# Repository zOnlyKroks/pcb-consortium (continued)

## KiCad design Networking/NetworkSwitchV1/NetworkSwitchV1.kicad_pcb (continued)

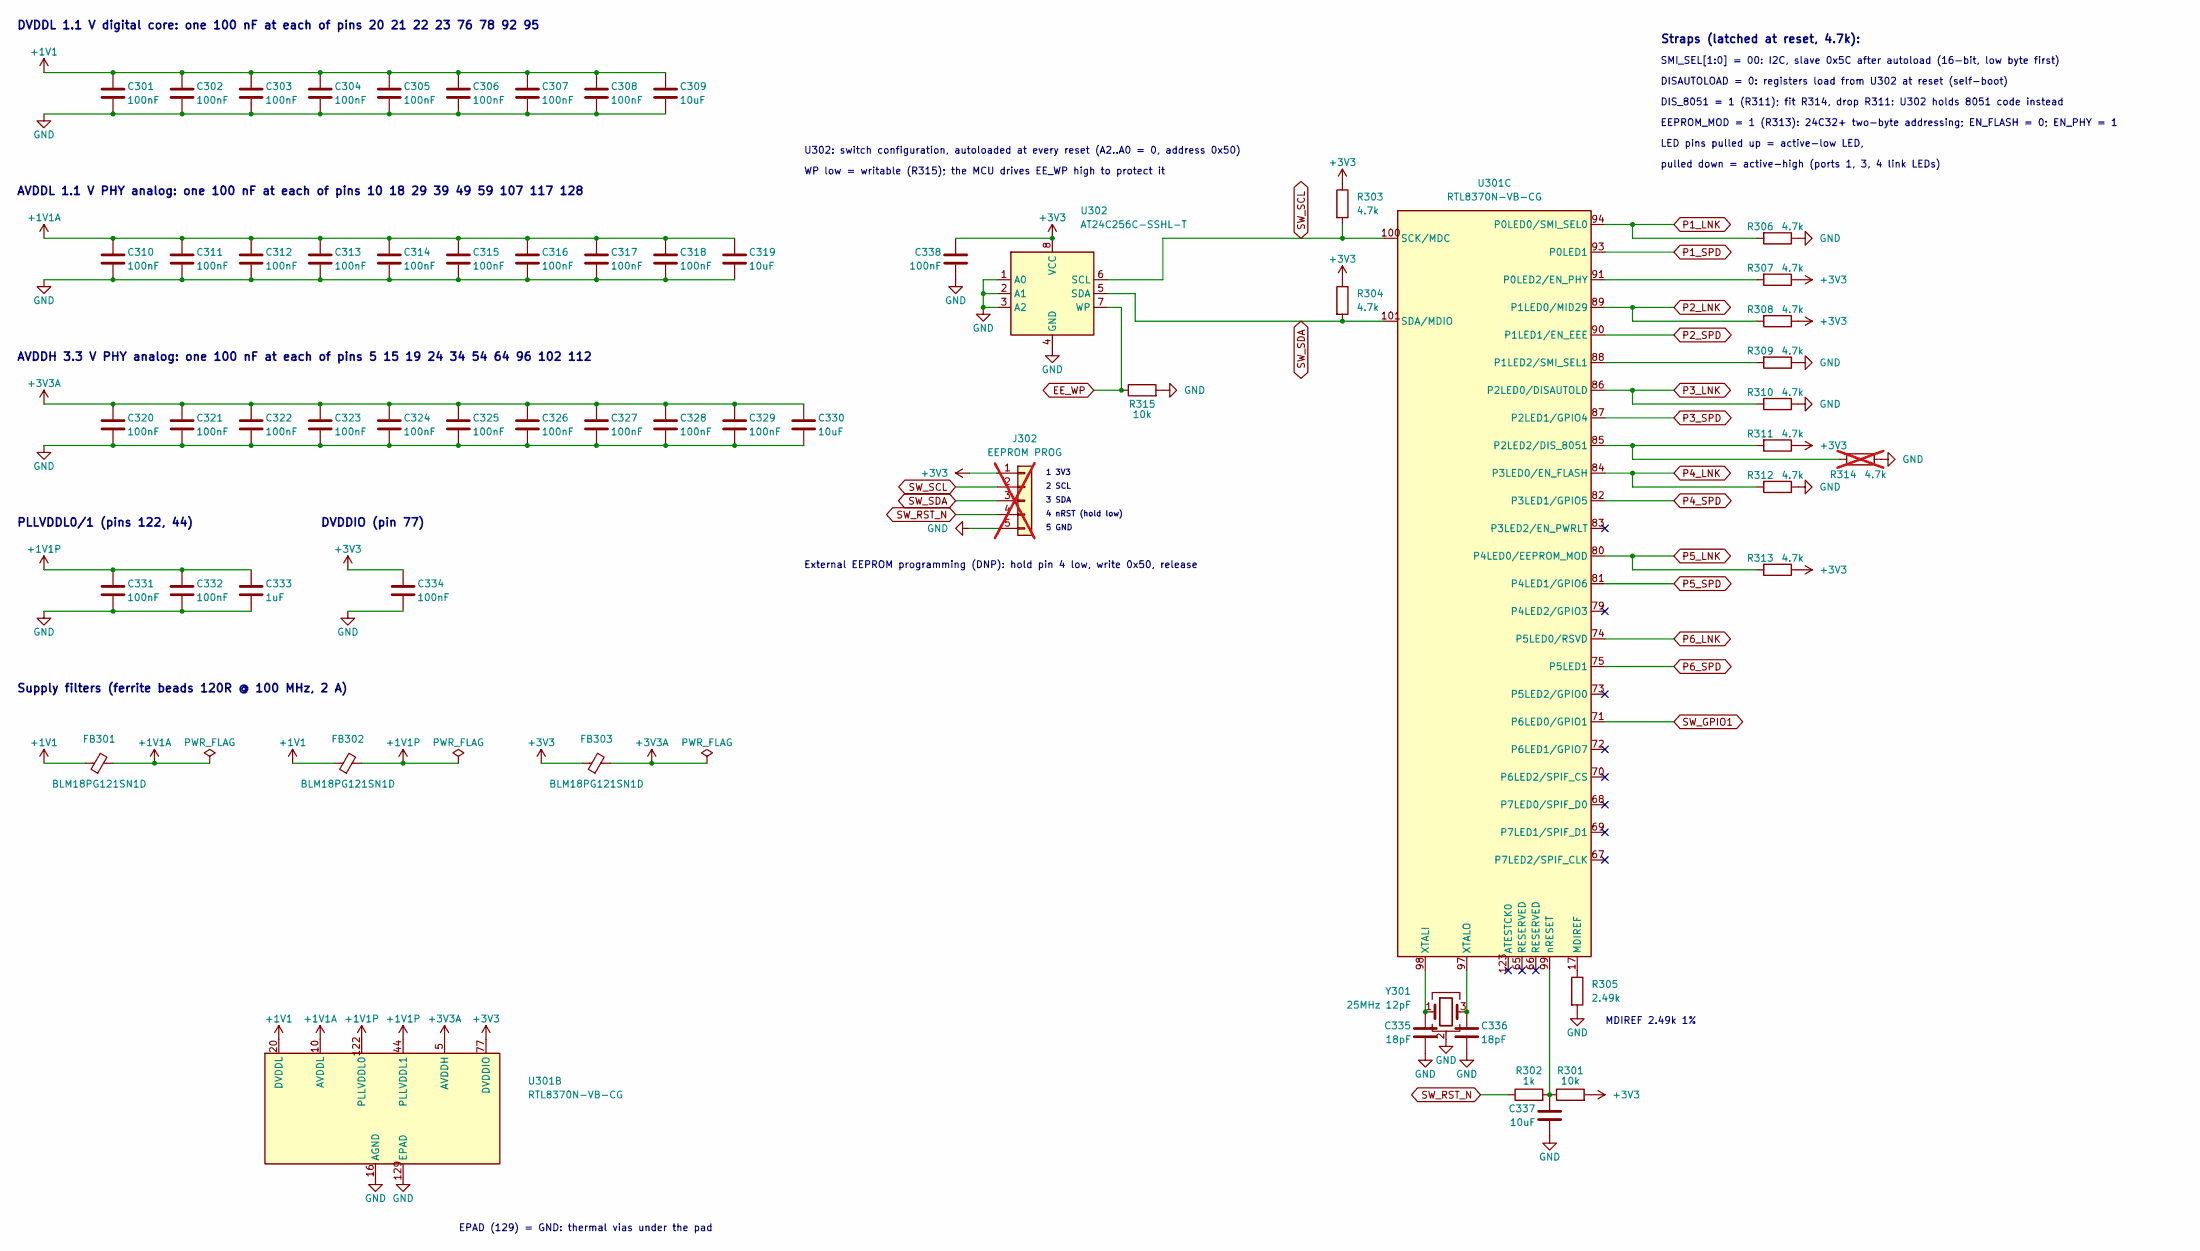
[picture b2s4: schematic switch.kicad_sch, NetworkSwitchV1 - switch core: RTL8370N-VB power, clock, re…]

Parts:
C301, C302, C303, C304, C305, C306, C307, C308, C310, C311, C312, C313, C314, C315, C316, C317, C318, C320, C321, C322, C323, C324, C325, C326, C327, C328, C329, C331, C332, C334, C338: 100nF; C_0603_1608Metric; LCSC Part # C14663
C309, C319, C330, C337: 10uF; C_0603_1608Metric; LCSC Part # C19702
C333: 1uF; C_0603_1608Metric; LCSC Part # C15849
C335, C336: 18pF; C_0603_1608Metric; LCSC Part # C1647
FB301, FB302, FB303: BLM18PG121SN1D; L_0603_1608Metric; LCSC Part # C14709
J302: EEPROM PROG; PinHeader_1x05_P2.54mm_Vertical; LCSC Part # C492404; not fitted
R301, R315: 10k; R_0603_1608Metric; LCSC Part # C25804
R302: 1k; R_0603_1608Metric; LCSC Part # C21190
R303, R304, R306, R307, R308, R309, R310, R311, R312, R313: 4.7k; R_0603_1608Metric; LCSC Part # C23162
R305: 2.49k; R_0603_1608Metric; LCSC Part # C22908
R314: 4.7k; R_0603_1608Metric; LCSC Part # C23162; not fitted
U301: RTL8370N-VB-CG; LQFP-128_L20.0-W14.0-P0.50-BL-EP7.0; LCSC Part # C2803243
U302: AT24C256C-SSHL-T; SOIC-8_3.9x4.9mm_P1.27mm; LCSC Part # C6482
Y301: 25MHz 12pF; Crystal_SMD_3225-4Pin_3.2x2.5mm; MPN X322525MOB4SI; LCSC Part # C9006

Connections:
+1V1: C301.1, C302.1, C303.1, C304.1, C305.1, C306.1, C307.1, C308.1, C309.1, FB301.1, FB302.1, U301.20 (DVDDL), U301.21 (DVDDL), U301.22 (DVDDL), U301.23 (DVDDL), U301.76 (DVDDL), U301.78 (DVDDL), U301.92 (DVDDL), U301.95 (DVDDL); also elsewhere on the board
+1V1A: C310.1, C311.1, C312.1, C313.1, C314.1, C315.1, C316.1, C317.1, C318.1, C319.1, FB301.2, U301.10 (AVDDL), U301.18 (AVDDL), U301.29 (AVDDL), U301.39 (AVDDL), U301.49 (AVDDL), U301.59 (AVDDL), U301.107 (AVDDL), U301.117 (AVDDL), U301.128 (AVDDL)
+1V1P: C331.1, C332.1, C333.1, FB302.2, U301.44 (PLLVDDL1), U301.122 (PLLVDDL0)
+3V3: C334.1, C338.1, FB303.1, J302.1, R301.2, R303.1, R304.1, R307.1, R308.1, R311.1, R313.1, U301.77 (DVDDIO), U302.8 (VCC); also elsewhere on the board
+3V3A: C320.1, C321.1, C322.1, C323.1, C324.1, C325.1, C326.1, C327.1, C328.1, C329.1, C330.1, FB303.2, U301.5 (AVDDH), U301.15 (AVDDH), U301.19 (AVDDH), U301.24 (AVDDH), U301.34 (AVDDH), U301.54 (AVDDH), U301.64 (AVDDH), U301.96 (AVDDH), U301.102 (AVDDH), U301.112 (AVDDH)
EE_WP: R315.1, U302.7 (WP); also elsewhere on the board
GND: C301.2, C302.2, C303.2, C304.2, C305.2, C306.2, C307.2, C308.2, C309.2, C310.2, C311.2, C312.2, C313.2, C314.2, C315.2, C316.2, C317.2, C318.2, C319.2, C320.2, C321.2, C322.2, C323.2, C324.2, C325.2, C326.2, C327.2, C328.2, C329.2, C330.2, C331.2, C332.2, C333.2, C334.2, C335.2, C336.2, C337.2, C338.2, J302.5, R305.2, R306.1, R309.1, R310.1, R312.1, R314.1, R315.2, U301.16 (AGND), U301.129 (EPAD), U302.1 (A0), U302.2 (A1), U302.3 (A2), U302.4 (GND), Y301.2 (G), Y301.4 (G); also elsewhere on the board
unnamed: R305.1, U301.17 (MDIREF)
unnamed: R307.2, U301.91 (P0LED2/EN_PHY)
unnamed: R309.2, U301.88 (P1LED2/SMI_SEL1)
unnamed: R311.2, R314.2, U301.85 (P2LED2/DIS_8051)
unnamed: C335.1, U301.98 (XTALI), Y301.1
unnamed: C336.1, U301.97 (XTALO), Y301.3
unnamed: C337.1, R301.1, R302.2, U301.99 (nRESET)
P1_LNK: R306.2, U301.94 (P0LED0/SMI_SEL0); also elsewhere on the board
P1_SPD: U301.93 (P0LED1); also elsewhere on the board
P2_LNK: R308.2, U301.89 (P1LED0/MID29); also elsewhere on the board
P2_SPD: U301.90 (P1LED1/EN_EEE); also elsewhere on the board
P3_LNK: R310.2, U301.86 (P2LED0/DISAUTOLD); also elsewhere on the board
P3_SPD: U301.87 (P2LED1/GPIO4); also elsewhere on the board
P4_LNK: R312.2, U301.84 (P3LED0/EN_FLASH); also elsewhere on the board
P4_SPD: U301.82 (P3LED1/GPIO5); also elsewhere on the board
P5_LNK: R313.2, U301.80 (P4LED0/EEPROM_MOD); also elsewhere on the board
P5_SPD: U301.81 (P4LED1/GPIO6); also elsewhere on the board
P6_LNK: U301.74 (P5LED0/RSVD); also elsewhere on the board
P6_SPD: U301.75 (P5LED1); also elsewhere on the board
SW_GPIO1: U301.71 (P6LED0/GPIO1); also elsewhere on the board
SW_RST_N: J302.4, R302.1; also elsewhere on the board
SW_SCL: J302.2, R303.2, U301.100 (SCK/MDC), U302.6 (SCL); also elsewhere on the board
SW_SDA: J302.3, R304.2, U301.101 (SDA/MDIO), U302.5 (SDA); also elsewhere on the board

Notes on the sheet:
DVDDIO (pin 77)
DVDDL 1.1 V digital core: one 100 nF at each of pins 20 21 22 23 76 78 92 95
1 3V3
Supply filters (ferrite beads 120R @ 100 MHz, 2 A)
DIS_8051 = 1 (R311); fit R314, drop R311: U302 holds 8051 code instead
LED pins pulled up = active-low LED,
AVDDL 1.1 V PHY analog: one 100 nF at each of pins 10 18 29 39 49 59 107 117 128
EPAD (129) = GND: thermal vias under the pad
Straps (latched at reset, 4.7k):
5 GND
PLLVDDL0/1 (pins 122, 44)
U302: switch configuration, autoloaded at every reset (A2..A0 = 0, address 0x50)
SMI_SEL[1:0] = 00: I2C, slave 0x5C after autoload (16-bit, low byte first)
MDIREF 2.49k 1%
pulled down = active-high (ports 1, 3, 4 link LEDs)
AVDDH 3.3 V PHY analog: one 100 nF at each of pins 5 15 19 24 34 54 64 96 102 112
External EEPROM programming (DNP): hold pin 4 low, write 0x50, release
WP low = writable (R315); the MCU drives EE_WP high to protect it
DISAUTOLOAD = 0: registers load from U302 at reset (self-boot)
3 SDA
EEPROM_MOD = 1 (R313): 24C32+ two-byte addressing; EN_FLASH = 0; EN_PHY = 1
4 nRST (hold low)
2 SCL

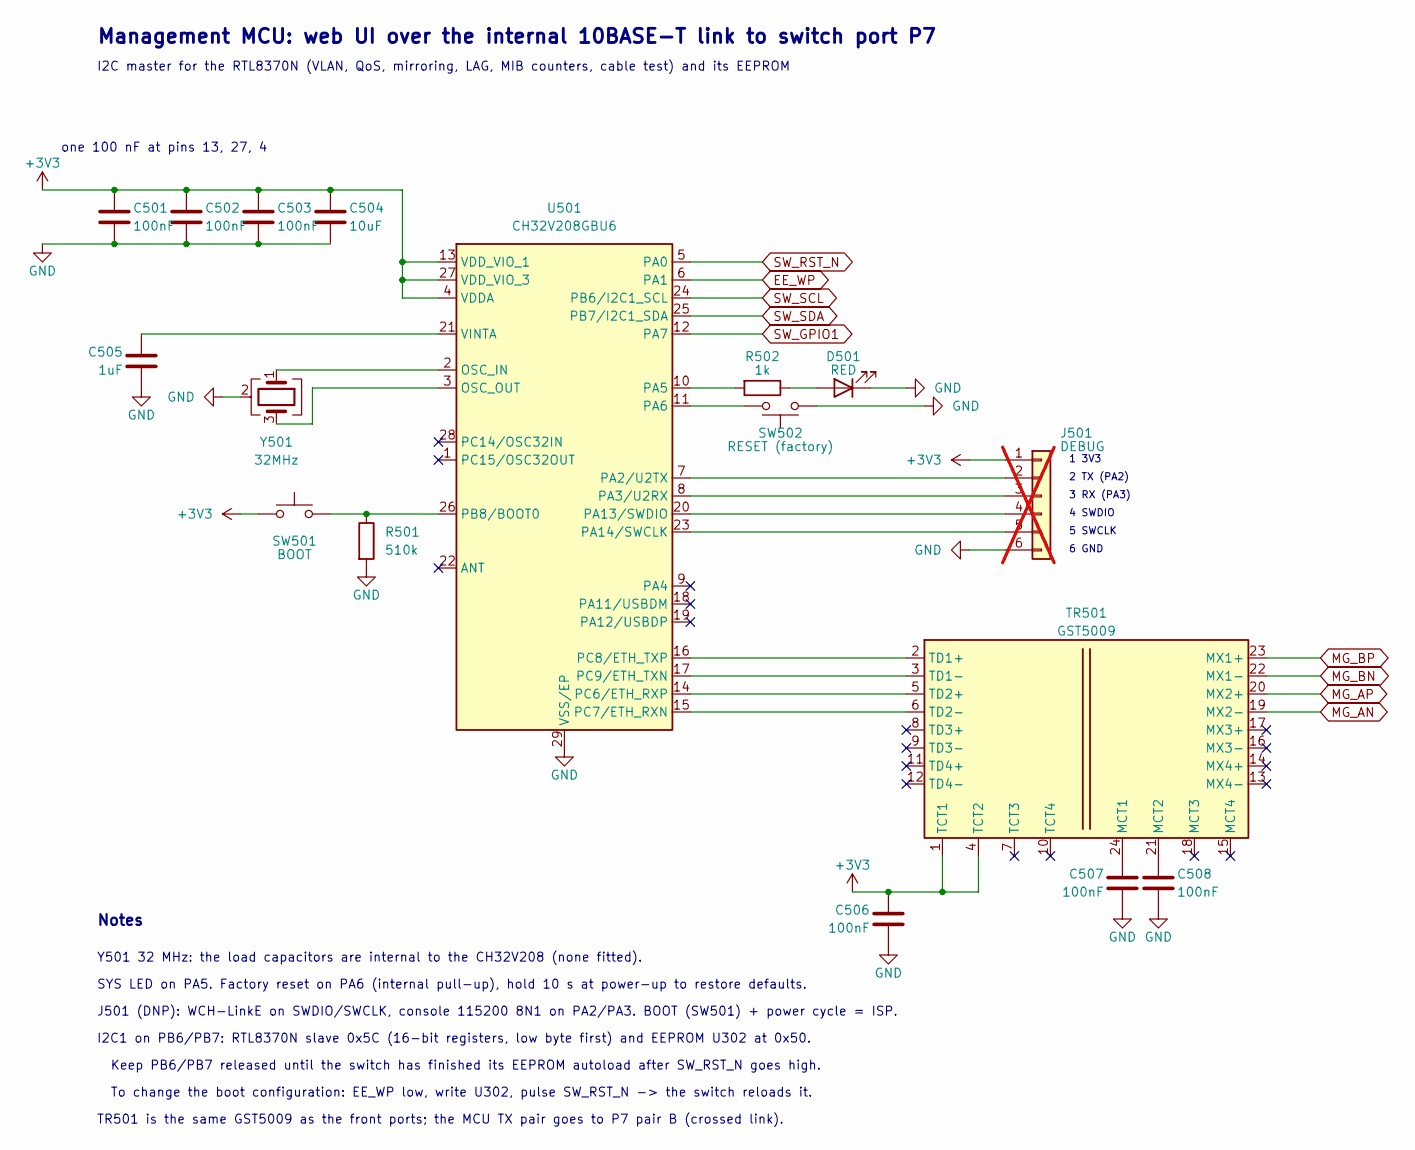
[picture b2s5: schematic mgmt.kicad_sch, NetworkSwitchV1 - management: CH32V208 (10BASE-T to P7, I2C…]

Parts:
C501, C502, C503, C506, C507, C508: 100nF; C_0603_1608Metric; LCSC Part # C14663
C504: 10uF; C_0603_1608Metric; LCSC Part # C19702
C505: 1uF; C_0603_1608Metric; LCSC Part # C15849
D501: RED; LED_0603_1608Metric; LCSC Part # C2286
J501: DEBUG; PinHeader_1x06_P2.54mm_Vertical; LCSC Part # C492405; not fitted
R501: 510k; R_0603_1608Metric; LCSC Part # C23192
R502: 1k; R_0603_1608Metric; LCSC Part # C21190
SW501: BOOT; SW-SMD_4P-L5.1-W5.1-P3.70-LS6.5-TL_H1.5; LCSC Part # C318884
SW502: RESET (factory); SW-SMD_4P-L5.1-W5.1-P3.70-LS6.5-TL_H1.5; LCSC Part # C318884
TR501: GST5009; XFMR-SMD_24P-L15.1-W7.1-P1.00-LS9.7-BL; LCSC Part # C55213474
U501: CH32V208GBU6; QFN-28_L4.0-W4.0-P0.40-BL-EP2.8; LCSC Part # C7434833
Y501: 32MHz; Crystal_SMD_3225-4Pin_3.2x2.5mm; MPN X322532MOB4SI; LCSC Part # C9009

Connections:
+3V3: C501.1, C502.1, C503.1, C504.1, C506.1, J501.1, SW501.1, SW501.2 (1), TR501.1 (TCT1), TR501.4 (TCT2), U501.4 (VDDA), U501.13 (VDD_VIO_1), U501.27 (VDD_VIO_3); also elsewhere on the board
EE_WP: U501.6 (PA1); also elsewhere on the board
GND: C501.2, C502.2, C503.2, C504.2, C505.2, C506.2, C507.2, C508.2, D501.1 (K), J501.6, R501.2, SW502.1, SW502.2 (1), U501.29 (VSS/EP), Y501.2 (G), Y501.4 (G); also elsewhere on the board
MG_AN: TR501.19 (MX2-); also elsewhere on the board
MG_AP: TR501.20 (MX2+); also elsewhere on the board
MG_BN: TR501.22 (MX1-); also elsewhere on the board
MG_BP: TR501.23 (MX1+); also elsewhere on the board
unnamed: D501.2 (A), R502.1
unnamed: J501.2, U501.7 (PA2/U2TX)
unnamed: J501.3, U501.8 (PA3/U2RX)
unnamed: J501.4, U501.20 (PA13/SWDIO)
unnamed: J501.5, U501.23 (PA14/SWCLK)
unnamed: C507.1, TR501.24 (MCT1)
unnamed: C508.1, TR501.21 (MCT2)
unnamed: TR501.2 (TD1+), U501.16 (PC8/ETH_TXP)
unnamed: TR501.3 (TD1-), U501.17 (PC9/ETH_TXN)
unnamed: TR501.5 (TD2+), U501.14 (PC6/ETH_RXP)
unnamed: TR501.6 (TD2-), U501.15 (PC7/ETH_RXN)
unnamed: U501.2 (OSC_IN), Y501.1
unnamed: U501.3 (OSC_OUT), Y501.3
unnamed: R502.2, U501.10 (PA5)
unnamed: SW502.3 (2), SW502.4 (2), U501.11 (PA6)
unnamed: R501.1, SW501.3 (2), SW501.4 (2), U501.26 (PB8/BOOT0)
unnamed: C505.1, U501.21 (VINTA)
SW_GPIO1: U501.12 (PA7); also elsewhere on the board
SW_RST_N: U501.5 (PA0); also elsewhere on the board
SW_SCL: U501.24 (PB6/I2C1_SCL); also elsewhere on the board
SW_SDA: U501.25 (PB7/I2C1_SDA); also elsewhere on the board

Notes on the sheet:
3 RX (PA3)
one 100 nF at pins 13, 27, 4
I2C1 on PB6/PB7: RTL8370N slave 0x5C (16-bit registers, low byte first) and EEPROM U302 at 0x50.
Keep PB6/PB7 released until the switch has finished its EEPROM autoload after SW_RST_N goes high.
Y501 32 MHz: the load capacitors are internal to the CH32V208 (none fitted).
4 SWDIO
Management MCU: web UI over the internal 10BASE-T link to switch port P7
6 GND
J501 (DNP): WCH-LinkE on SWDIO/SWCLK, console 115200 8N1 on PA2/PA3. BOOT (SW501) + power cycle = ISP.
5 SWCLK
TR501 is the same GST5009 as the front ports; the MCU TX pair goes to P7 pair B (crossed link).
To change the boot configuration: EE_WP low, write U302, pulse SW_RST_N -> the switch reloads it.
Notes
SYS LED on PA5. Factory reset on PA6 (internal pull-up), hold 10 s at power-up to restore defaults.
1 3V3
I2C master for the RTL8370N (VLAN, QoS, mirroring, LAG, MIB counters, cable test) and its EEPROM
2 TX (PA2)

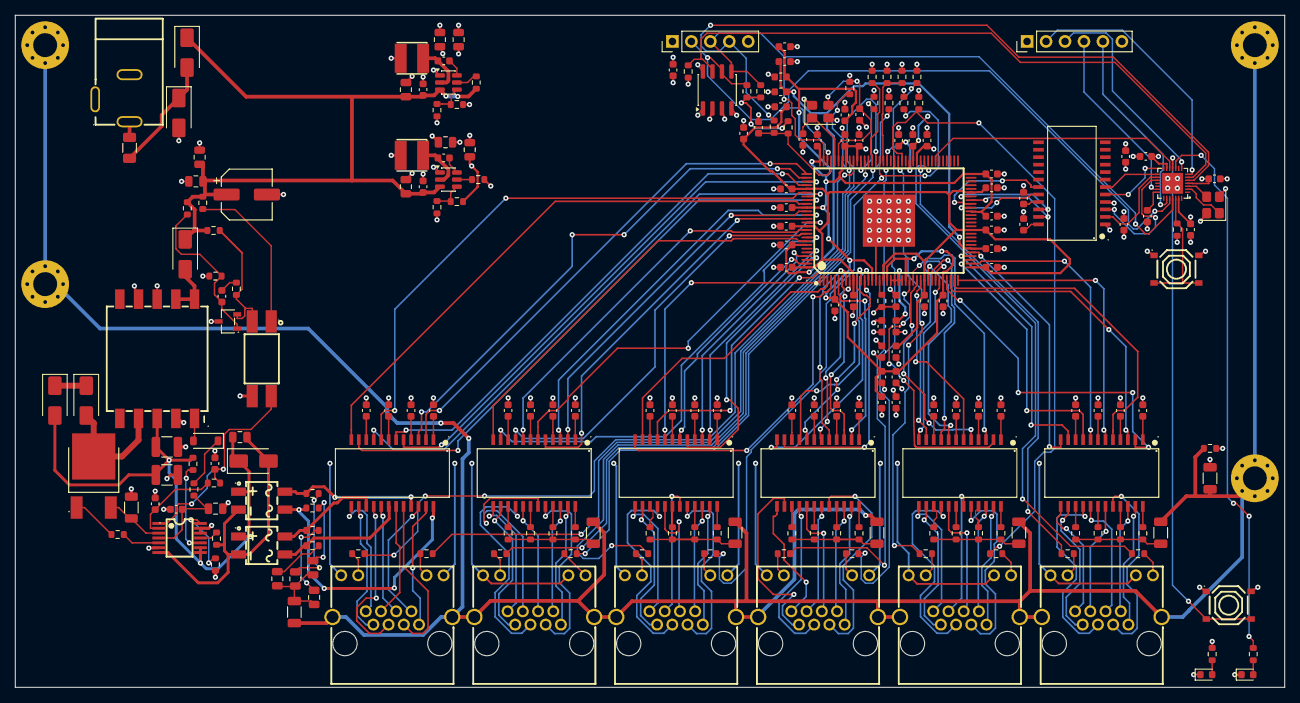
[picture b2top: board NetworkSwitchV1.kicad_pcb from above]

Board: 4 copper layers, 170.0 x 90.0 mm, 226 parts (0 on the bottom side), 251 nets.

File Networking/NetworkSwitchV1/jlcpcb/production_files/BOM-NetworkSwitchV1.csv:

Comment,Designator,Footprint,LCSC,Quantity
0.43R,R107,R_1206_3216Metric,C24965,1
1.1A 16V,F101,Fuse_1206_3216Metric,C7542961,1
100k,R114,R_0603_1608Metric,C25803,1
100nF,"C102,C113,C114,C118,C119,C301,C302,C303,C304,C305,C306,C307,C308,C310,C311,C312,C313,C314,C315,C316,C317,C318,C320,C321,C322,C323,C324,C325,C326,C327,C328,C329,C331,C332,C334,C338,C411,C412,C413,C414,C421,C422,C423,C424,C431,C432,C433,C434,C441,C442,C443,C444,C451,C452,C453,C454,C461,C462,C463,C464,C501,C502,C503,C506,C507,C508",C_0603_1608Metric,C14663,66
100nF 100V,"C101,C151,C152,C153,C154",C_0805_2012Metric,C28233,5
100uF 25V,C108,CP_Elec_6.3x7.7,C970685,1
10R,"R105,R106",R_0603_1608Metric,C22859,2
10k,"R104,R109,R113,R116,R117,R119,R301,R315",R_0603_1608Metric,C25804,8
10nF,C111,C_0603_1608Metric,C57112,1
10uF,"C309,C319,C330,C337,C504",C_0603_1608Metric,C19702,5
10uF 25V,"C112,C117",C_0805_2012Metric,C15850,2
18pF,"C335,C336",C_0603_1608Metric,C1647,2
1M,R401,R_0603_1608Metric,C22935,1
1N4148W,D104,D_SOD-123,C81598,1
1k,"R110,R120,R302,R502",R_0603_1608Metric,C21190,4
1nF,C103,C_0603_1608Metric,C1588,1
1nF 2kV,"C155,C401,C425,C435,C445,C455,C465",C_1206_3216Metric,C9196,7
1uF,"C104,C333,C505",C_0603_1608Metric,C15849,3
2.2uF 100V,"C106,C107",C_1210_3225Metric,C55151,2
2.2uH,"L101,L102",IND-SMD_L4.0-W4.0_FNR40XXS,C167869,2
2.49k,R305,R_0603_1608Metric,C22908,1
22uF 25V,"C105,C109,C110,C115,C116,C120,C121",C_0805_2012Metric,C45783,7
24.9k,R101,R_0603_1608Metric,C25962,1
25MHz 12pF,Y301,Crystal_SMD_3225-4Pin_3.2x2.5mm,C9006,1
32MHz,Y501,Crystal_SMD_3225-4Pin_3.2x2.5mm,C9009,1
33k,R115,R_0603_1608Metric,C4216,1
39k,R108,R_0603_1608Metric,C23153,1
4.3k,R118,R_0603_1608Metric,C23159,1
4.7k,"R112,R303,R304,R306,R307,R308,R309,R310,R311,R312,R313",R_0603_1608Metric,C23162,11
510R,"R415,R416,R425,R426,R435,R436,R445,R446,R455,R456,R465,R466",R_0603_1608Metric,C23193,12
510k,R501,R_0603_1608Metric,C23192,1
56k,R103,R_0603_1608Metric,C23206,1
75R,"R151,R152,R153,R154,R421,R422,R423,R424,R431,R432,R433,R434,R441,R442,R443,R444,R451,R452,R453,R454,R461,R462,R463,R464",R_0603_1608Metric,C4275,24
90.9R,R102,R_0603_1608Metric,C23130,1
AT24C256C-SSHL-T,U302,SOIC-8_3.9x4.9mm_P1.27mm,C6482,1
BLM18PG121SN1D,"FB301,FB302,FB303",L_0603_1608Metric,C14709,3
BOOT,SW501,SW-SMD_4P-L5.1-W5.1-P3.70-LS6.5-TL_H1.5,C318884,1
CH32V208GBU6,U501,QFN-28_L4.0-W4.0-P0.40-BL-EP2.8,C7434833,1
CJ431,U102,SOT-23-3_L2.9-W1.6-P1.90-LS2.8-BR,C3113,1
DC-005,J101,DC-IN-TH_DC-005-5.5-2.0,C16214,1
EP1322S-10,T101,XFMR-SMD_EP1322S-10,C37328796,1
GST5009,"TR401,TR402,TR403,TR404,TR405,TR406,TR501",XFMR-SMD_24P-L15.1-W7.1-P1.00-LS9.7-BL,C55213474,7
IRFR220N,Q101,TO-252-2_L6.6-W6.1-P4.57-LS9.9-BR-CW,C22365390,1
LTV-817S,U103,OPTO-SMD-4_L4.6-W6.5-P2.54-LS10.3-BL,C109227,1
MB10S,"BR101,BR102",MBS_L4.7-W3.8-P2.40-LS7.0-TL,C2488,2
RED,"D108,D501",LED_0603_1608Metric,C2286,2
RESET (factory),SW502,SW-SMD_4P-L5.1-W5.1-P3.70-LS6.5-TL_H1.5,C318884,1
RJ45-202-007-02,"J401,J402,J403,J404,J405,J406",RJ45-TH_RJ45-202-007-02,C7421418,6
RTL8370N-VB-CG,U301,LQFP-128_L20.0-W14.0-P0.50-BL-EP7.0,C2803243,1
SMAJ13A,D106,D_SMA,C19077533,1
SMAJ58A,"D101,D103",D_SMA,C19077554,2
SS210,D105,D_SMA,C14996,1
SS34,D107,D_SMA,C8678,1
TPS23753APWR,U101,TSSOP-14_L5.0-W4.4-P0.65-LS6.4-BL,C92115,1
TPS563201DDCR,"U104,U105",TSOT-23-6,C116592,2
US1M,D102,D_SMA,C412437,1
M3,H403,MountingHole_3.2mm_M3_Pad_Via,,1
M3,H402,MountingHole_3.2mm_M3_Pad_Via,,1
M3,H404,MountingHole_3.2mm_M3_Pad_Via,,1
M3,H401,MountingHole_3.2mm_M3_Pad_Via,,1

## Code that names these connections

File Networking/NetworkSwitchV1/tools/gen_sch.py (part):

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    sh.wire("U301.3.100", (231.14, ysc), (231.14, 83.82), "U302.6")
    sh.wire("U301.3.101", (226.06, ysd), (226.06, 86.36), "U302.5")
    sh.wire((xs - 15.24, ysc), (xs - 15.24, ysc - 5.08), (xs - 20.32, ysc - 5.08))
    sh.glabel("SW_SCL", (xs - 20.32, ysc - 5.08), 180)
    sh.wire((xs - 15.24, ysd), (xs - 15.24, ysd + 5.08), (xs - 20.32, ysd + 5.08))
    sh.glabel("SW_SDA", (xs - 20.32, ysd + 5.08), 180)
    sh.power("+3V3", "U302.8")
    sh.wire("U302.8", (193.04, 76.2))
    C(sh, "C338", "100nF", 193.04, 80.01, fields="L")
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    sh.power("GND", (198.12, 88.9))
    sh.power("GND", "U302.4")
    sh.wire("U302.7", (223.52, 88.9), (223.52, 104.14), (218.44, 104.14))
    sh.glabel("EE_WP", (218.44, 104.14), 180)
    R(sh, "R315", "10k", 227.33, 96.52, rot=90, fields="B")
    sh.wire((223.52, 96.52), "R315.1")
    sh.power("GND", "R315.2", rot=90)
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           fields=((205.74, 113.03, None), (205.74, 115.57, None)))
    sh.wire("J302.1", (195.58, sh.P("J302.1")[1]))
    sh.power("+3V3", (195.58, sh.P("J302.1")[1]), rot=90)
    for pin, net in (("2", "SW_SCL"), ("3", "SW_SDA"), ("4", "SW_RST_N")):
        sh.glabel(net, sh.stub("J302." + pin, -7.62, 0), 180)
    sh.wire("J302.5", (195.58, sh.P("J302.5")[1]))
    sh.power("GND", (195.58, sh.P("J302.5")[1]), rot=270)
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    sh.power("+3V3", "R301.2", rot=270)
    R(sh, "R302", "1k", xr - 3.81, jr, rot=90, fields="T")
    sh.wire("R302.1", (xr - 12.7, jr))
    sh.glabel("SW_RST_N", (xr - 12.7, jr), 180)
    # bias resistor
    xm = sh.P("U301.3.17")[0]
    R(sh, "R305", "2.49k", xm, yb + 3.81, fields="R")
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            ("84", "P4_LNK", "GND", "R312"), ("82", "P4_SPD", None, None), ("83", None, None, None),
            ("80", "P5_LNK", "+3V3", "R313"), ("81", "P5_SPD", None, None), ("79", None, None, None),
            ("74", "P6_LNK", None, None), ("75", "P6_SPD", None, None), ("73", None, None, None),
            ("71", "SW_GPIO1", None, None), ("72", None, None, None), ("70", None, None, None),
            ("68", None, None, None), ("69", None, None, None), ("67", None, None, None)]
    for pin, net, pull, ref in rows:
        spec = "U301.3." + pin
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    sh.power("+3V3", (137.16, yb), rot=90)
    sh.power("GND", "U501.29")
    # switch control + I2C bus
    for pin, net in (("5", "SW_RST_N"), ("6", "EE_WP"), ("24", "SW_SCL"), ("25", "SW_SDA"), ("12", "SW_GPIO1")):
        sh.glabel(net, sh.stub("U501." + pin, 10.16, 0), 0)
    # status LED + factory-reset button
    y5, y6 = sh.P("U501.10")[1], sh.P("U501.11")[1]
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    sh.wire("U501.11", "SW502.3")
    sh.wire("SW502.1", (233.68, y6))
    sh.power("GND", (233.68, y6), rot=90)
    # debug header: 3V3, TX, RX, SWDIO, SWCLK, GND (straight across from PA2/PA3/PA13/PA14)
    ytx = sh.P("U501.7")[1]
    hx = 250.19
    sh.add("J501", "Connector_Generic:Conn_01x06", hx, ytx + 2.54, value="DEBUG", dnp=True,
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    sh.power("+3V3", (hx - 10.16, sh.P("J501.1")[1]), rot=90)
    sh.wire("J501.6", (hx - 10.16, sh.P("J501.6")[1]))
    sh.power("GND", (hx - 10.16, sh.P("J501.6")[1]), rot=270)
    for k, s_ in enumerate(("1 3V3", "2 TX (PA2)", "3 RX (PA3)", "4 SWDIO", "5 SWCLK", "6 GND")):
        T(s_, hx + 3.81, sh.P("J501.%d" % (k + 1))[1] + 0.635, 1.016)
    for pin in ("9", "18", "19"):
        sh.nc("U501." + pin)
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    T("Notes", 116.84, 200.66, 1.524, True)
    for k, s_ in enumerate((
            "Y501 32 MHz: the load capacitors are internal to the CH32V208 (none fitted).",
            "SYS LED on PA5. Factory reset on PA6 (internal pull-up), hold 10 s at power-up to restore defaults.",
            "J501 (DNP): WCH-LinkE on SWDIO/SWCLK, console 115200 8N1 on PA2/PA3. BOOT (SW501) + power cycle = ISP.",
            "I2C1 on PB6/PB7: RTL8370N slave 0x5C (16-bit registers, low byte first) and EEPROM U302 at 0x50.",
            "  Keep PB6/PB7 released until the switch has finished its EEPROM autoload after SW_RST_N goes high.",
            "  To change the boot configuration: EE_WP low, write U302, pulse SW_RST_N -> the switch reloads it.",
            "TR501 is the same GST5009 as the front ports; the MCU TX pair goes to P7 pair B (crossed link).")):
        T(s_, 116.84, 205.74 + 3.81 * k)
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              (sheets[1][0], 132.08, 101.6, 63.5, 38.1, "Switch core: RTL8370N"),
              (sheets[2][0], 226.06, 101.6, 63.5, 38.1, "Ports 1-6 + magnetics"),
              (sheets[3][0], 320.04, 101.6, 63.5, 38.1, "Management: CH32V208")]
    T("Cross-sheet nets are global labels: P<n>_LNK / P<n>_SPD (LEDs), SW_SCL / SW_SDA / SW_RST_N / EE_WP / SW_GPIO1,",
      25.4, 167.64, 1.524)
    T("MG_AP/AN/BP/BN (management link), POE_CT1..4 (port 1 centre taps)", 25.4, 172.72, 1.524)
    tb = title_block(prj, "NetworkSwitchV1 - 6-port managed gigabit switch, PoE powered", DATE, REV,
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
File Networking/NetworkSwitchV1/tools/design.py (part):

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u.update({"98": "XTALI", "97": "XTALO", "99": "SW_NRST", "100": "SW_SCL", "101": "SW_SDA", "17": "MDIREF"})
u.update({"94": "P1_LNK", "93": "P1_SPD", "91": "STRAP_EN_PHY", "89": "P2_LNK", "90": "P2_SPD", "88": "STRAP_SMI_SEL1",
          "86": "P3_LNK", "87": "P3_SPD", "85": "STRAP_DIS_8051", "84": "P4_LNK", "82": "P4_SPD",
          "80": "P5_LNK", "81": "P5_SPD", "74": "P6_LNK", "75": "P6_SPD", "71": "SW_GPIO1"})
part("U301", u)
part("FB301", {"1": "+1V1", "2": "+1V1A"})
part("FB302", {"1": "+1V1", "2": "+1V1P"})
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part("R303", {"1": "+3V3", "2": "SW_SCL"})
part("R304", {"1": "+3V3", "2": "SW_SDA"})
part("R305", {"1": "MDIREF", "2": "GND"})                                   # 2.49k 1%
part("R306", {"1": "P1_LNK", "2": "GND"})                                   # SMI_SEL0 = 0
part("R307", {"1": "STRAP_EN_PHY", "2": "+3V3"})                            # EN_PHY = 1
part("R308", {"1": "P2_LNK", "2": "+3V3"})                                  # MID29 = 1 (unused in I2C mode)
part("R309", {"1": "STRAP_SMI_SEL1", "2": "GND"})                           # SMI_SEL[1:0] = 00 -> I2C, LSB first
part("R310", {"1": "P3_LNK", "2": "GND"})                                   # DISAUTOLOAD = 0 -> EEPROM autoload
part("R311", {"1": "STRAP_DIS_8051", "2": "+3V3"})                          # DIS_8051 = 1: EEPROM = registers
part("R314", {"1": "STRAP_DIS_8051", "2": "GND"})                           # DNP option: run 8051 code from EEPROM
part("R312", {"1": "P4_LNK", "2": "GND"})                                   # EN_FLASH = 0
part("R313", {"1": "P5_LNK", "2": "+3V3"})                                  # EEPROM_MOD = 1 (24C32+, 2-byte address)
# configuration EEPROM (autoload at reset; written by the MCU or through J302)
part("U302", {"8": "+3V3", "4": "GND", "1": "GND", "2": "GND", "3": "GND", "6": "SW_SCL", "5": "SW_SDA", "7": "EE_WP"})
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# ======================================================================= mgmt.kicad_sch (5xx)
part("U501", {"13": "+3V3", "27": "+3V3", "4": "+3V3", "29": "GND", "21": "VINTA", "2": "OSC_IN", "3": "OSC_OUT",
              "26": "BOOT0", "5": "SW_RST_N", "6": "EE_WP", "7": "UART_TX", "8": "UART_RX", "24": "SW_SCL", "25": "SW_SDA",
              "10": "LED_SYS", "11": "BTN_RST", "12": "SW_GPIO1", "20": "SWDIO", "23": "SWCLK",
              "16": "ETH_TXP", "17": "ETH_TXN", "14": "ETH_RXP", "15": "ETH_RXN"})
for c in ("C501", "C502", "C503", "C504"):
    part(c, {"1": "+3V3", "2": "GND"})
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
